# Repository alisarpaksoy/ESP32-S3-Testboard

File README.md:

# ESP32-S3 Testboard

## Overview

This project is a custom ESP32-S3 testboard designed in KiCad. The board was created as a compact development and testing platform for the ESP32-S3-WROOM module.

The board includes USB-C power and data connection, 3.3 V voltage regulation, boot and reset buttons, a user button, RGB LED, Qwiic I2C connector, GPIO headers, and an onboard Si7021-A20 temperature and humidity sensor.

The purpose of this project is to practice PCB design, ESP32-S3 hardware design, sensor integration, and GitHub-based engineering documentation.

## Main Features

* ESP32-S3-WROOM module
* USB-C connector for power and USB communication
* 5 V input from USB-C
* 3.3 V regulated power supply
* Boot and reset buttons
* User button
* RGB LED
* Si7021-A20 temperature and humidity sensor
* Qwiic I2C connector
* GPIO/SPI breakout headers
* ESD protection components
* Mounting holes
* ESP32-S3 antenna keepout area

## Hardware Description

### ESP32-S3 Module

The main microcontroller of the board is the ESP32-S3-WROOM module. It provides Wi-Fi, Bluetooth Low Energy, GPIO, USB, I2C, SPI, UART, PWM, ADC, and other peripheral interfaces.

The board exposes several ESP32-S3 pins through headers so the module can be used for testing and prototyping.

### Power Supply

The board is powered through the USB-C connector. The USB 5 V input is protected using a polyfuse and then regulated to 3.3 V using an LDO regulator.

The 3.3 V rail powers the ESP32-S3 module, Si7021 sensor, RGB LED, Qwiic connector, and supporting circuits.

### USB-C Interface

The USB-C connector provides power and USB data communication. The USB D+ and D− lines are connected to the ESP32-S3 USB pins for programming and serial communication.

### Boot and Reset Circuit

The board includes dedicated boot and reset buttons. The boot button is connected to GPIO0, and the reset button is connected to the ESP32-S3 enable/reset line.

These buttons allow the ESP32-S3 to be reset and placed into programming mode during firmware upload.

### Si7021 Temperature and Humidity Sensor

The board includes the Si7021-A20 digital temperature and humidity sensor. It communicates with the ESP32-S3 using the I2C bus.

This sensor can be used for:

* Temperature measurement
* Humidity measurement
* Environmental monitoring
* I2C communication testing

### Qwiic I2C Connector

A Qwiic connector is included for connecting external I2C modules. The connector provides:

* GND
* 3.3 V
* SDA
* SCL

Pull-up resistors are included on the I2C lines.

### RGB LED

The RGB LED is connected to ESP32-S3 GPIO pins through current-limiting resistors. It can be used for status indication, firmware testing, and GPIO output testing.

## Repository Structure

```text
ESP32-S3-Testboard/
│
├── README.md
├── .gitignore
│
├── kicad/
│   ├── ESP32-S3.kicad_pro
│   ├── ESP32-S3.kicad_sch
│   └── ESP32-S3.kicad_pcb
│
├── Images/
│   ├── schematic.png
│   ├── pcb_layout.png
│   └── pcb_3d_view.png
│
├── Documentation/
│   └── Datasheets/
│       ├── esp32-s3-wroom-1_wroom-1u_datasheet_en.pdf
│       └── Si7021-A20_datasheet.pdf
│
└── Manufacturing/
    ├── Gerbers/
    └── Drill/
```

## KiCad Project

The KiCad design files are located in the `kicad/` folder.

To open the project:

1. Install KiCad.
2. Open the `.kicad_pro` file.
3. Review the schematic and PCB layout.
4. Run ERC and DRC before modifying or manufacturing the board.

## Images

Project images are located in the `Images/` folder.

Included images:

* Schematic screenshot
* PCB layout screenshot
* 3D PCB render

## Manufacturing

Manufacturing files will be placed in the `Manufacturing/` folder.

Before ordering the PCB, the following checks should be completed:

* Electrical Rules Check
* Design Rules Check
* Gerber preview inspection
* Drill file verification
* USB-C footprint check
* ESP32-S3 footprint orientation check
* ESP32-S3 antenna keepout check
* Power trace width check
* I2C pull-up resistor verification

## Project Status

* [x] Schematic completed
* [x] PCB layout completed
* [x] ESP32-S3 module added
* [x] USB-C interface added
* [x] 3.3 V regulator added
* [x] Si7021 sensor added
* [x] Qwiic connector added
* [x] RGB LED added
* [ ] PCB manufactured
* [ ] Board assembled
* [ ] Power supply tested
* [ ] USB programming tested
* [ ] Si7021 sensor tested
* [ ] Example firmware added

## Author

Ali Sarp Aksoy
Mechatronics Engineering Student
Kraków, Poland

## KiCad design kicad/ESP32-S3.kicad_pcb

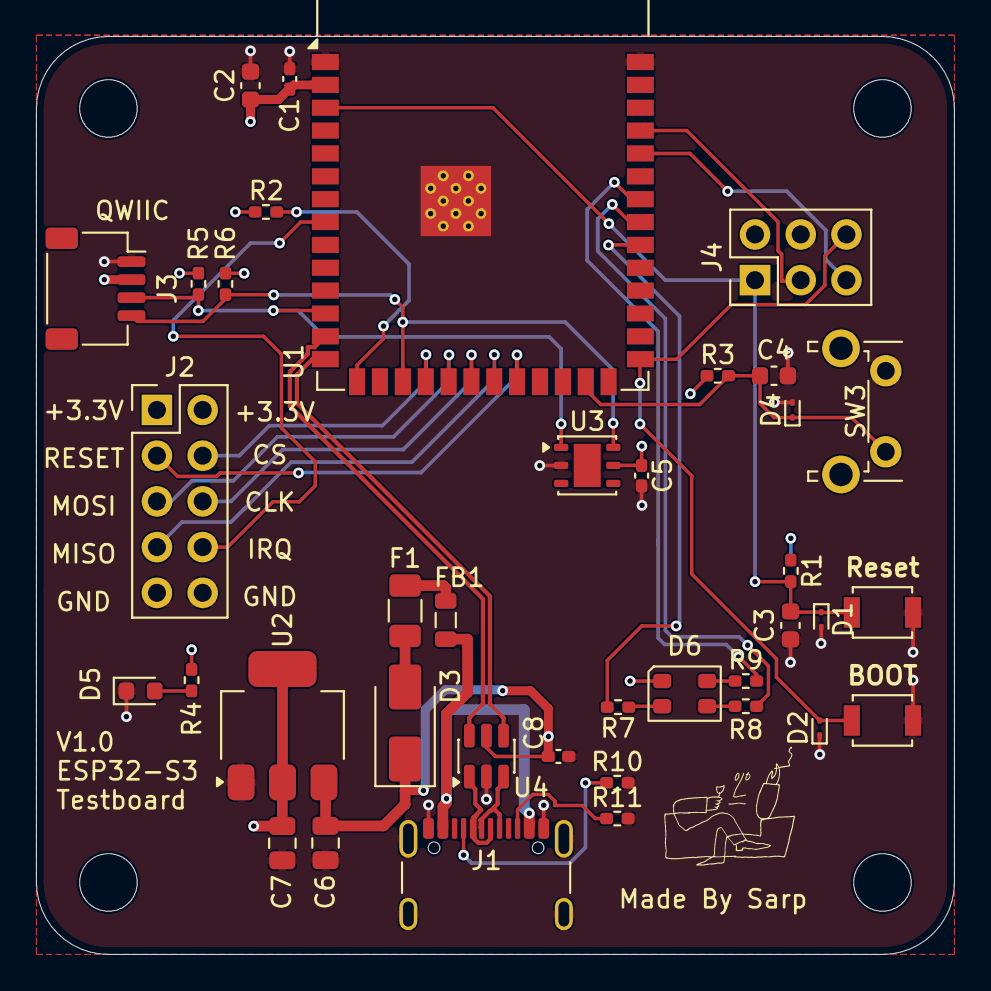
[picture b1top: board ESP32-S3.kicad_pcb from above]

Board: 4 copper layers, 51.0 x 51.0 mm, 42 parts (0 on the bottom side), 33 nets.

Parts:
C1, C5, C8: 100n; C_0402_1005Metric_Pad0.74x0.62mm_HandSolder
C2: 10u; C_0603_1608Metric
C3, C4: 1u; C_0603_1608Metric
C6, C7: 22u; C_0805_2012Metric
D1, D2, D4: ESD3.3; D_SOD-923
D3: 1N5817; D_SMA
D5: Green; LED_0603_1608Metric
D6: CLV1L-FKB; LED_Cree-PLCC4_3.2x2.8mm_CCW
F1: Polyfuse 1A; Fuse_1206_3216Metric
FB1: BLM21PG220; L_0805_2012Metric
H1, H2, H3, H4: MountingHole; MountingHole_3.2mm_M3
J1: USB_C_Receptacle_USB2.0_16P; USB_C_Receptacle_GCT_USB4105-xx-A_16P_TopMnt_Horizontal
J2: Conn_02x03_Odd_Even; PinHeader_2x05_P2.54mm_Vertical
J3: Conn_01x04; JST_SH_SM04B-SRSS-TB_1x04-1MP_P1.00mm_Horizontal
J4: Pin_2x5; PinHeader_2x03_P2.54mm_Vertical
R1, R2, R3: 10K; R_0402_1005Metric_Pad0.72x0.64mm_HandSolder
R4, R7, R8, R9: 1K; R_0402_1005Metric_Pad0.72x0.64mm_HandSolder
R5, R6: 2K2; R_0402_1005Metric_Pad0.72x0.64mm_HandSolder
R10, R11: 5.1K; R_0402_1005Metric_Pad0.72x0.64mm_HandSolder
SW1: BOOT; SW_SPST_B3U-1000P
SW2: Reset; SW_SPST_B3U-1000P
SW3: USER_SW; SW_Tactile_SPST_Angled_PTS645Vx31-2LFS
U1: ESP32-S3-WROOM-1
U2: LM1117DT-3.3; SOT-223
U3: Si7021-A20; DFN-6-1EP_3x3mm_P1mm_EP1.5x2.4mm
U4: USBLC6-2SC6; SOT-23-6

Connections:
+3.3V: C1.1, C2.1, C5.1, C7.1, D6.1 (A), J2.1, J2.2, J3.2, J4.2, R1.1, R2.2, R3.1, R4.1, R5.1, R6.1, U1.2 (3V3), U2.2 (VO), U2.4, U3.5 (VDD)
+5V: C6.1, C8.1, D3.1 (K), U2.3 (VI), U4.5 (VBUS)
/B_LED: R9.2, U1.34 (IO41)
/CC1: J1.A5 (CC1), R10.1
/CC2: J1.B5 (CC2), R11.1
/CLK: J2.6, U1.20 (IO12)
/CS: J2.4, U1.18 (IO10)
/D+: J1.A6 (D+), J1.B6 (D+), U4.3 (I/O2)
/D-: J1.A7 (D-), J1.B7 (D-), U4.1 (I/O1)
/ESP_EN: C3.1, D1.1 (A1), J4.1, R1.2, SW2.2 (B), U1.3 (EN)
/ESP_IO0: D2.2 (A2), J4.6, SW1.2 (B), U1.27 (IO0)
/ESP_RXD: J4.5, U1.36 (RXD0)
/ESP_TXD: J4.3, U1.37 (TXD0)
/G_LED: R8.2, U1.33 (IO40)
/IRQ: J2.8, U1.8 (IO15)
/MISO: J2.7, U1.21 (IO13)
/MOSI: J2.5, U1.19 (IO11)
/RESET: J2.3, U1.22 (IO14)
/R_LED: R7.2, U1.32 (IO39)
/SCL: J3.4, R6.2, U1.17 (IO9), U3.6 (SCL)
/SDA: J3.3, R5.2, U1.12 (IO8), U3.1 (SDA)
/USB_D+: U1.14 (USB_D+), U4.4 (I/O2)
/USB_D-: U1.13 (USB_D-), U4.6 (I/O1)
/USER_SW: C4.1, D4.1 (A1), R3.2, SW3.2 (B), U1.25 (IO48)
GND: C1.2, C2.2, C3.2, C4.2, C5.2, C6.2, C7.2, C8.2, D1.2 (A2), D2.1 (A1), D4.2 (A2), D5.1 (K), J1.A1 (GND), J1.A12 (GND), J1.B1 (GND), J1.B12 (GND), J1.SH (SHIELD), J2.9, J2.10, J3.1, J4.4, R10.2, R11.2, SW1.1 (A), SW2.1 (A), SW3.1 (A), U1.1 (GND), U1.40 (GND), U1.41 (GND), U2.1 (GND), U3.2 (GND), U4.2 (GND)
unnamed: D3.2 (A), F1.1
unnamed: D5.2 (A), R4.2
unnamed: D6.4 (BK), R9.1
unnamed: D6.3 (GK), R8.1
unnamed: D6.2 (RK), R7.1
unnamed: FB1.1, J1.A4 (VBUS), J1.A9 (VBUS), J1.B4 (VBUS), J1.B9 (VBUS)
unnamed: F1.2, FB1.2
unnamed: R2.1, U1.15 (IO3)

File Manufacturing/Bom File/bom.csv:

Designator,Footprint,Quantity,Value,LCSC Part #
"C1, C5, C8",0402,3,100n,
C2,0603,1,10u,
"C3, C4",0603,2,1u,
"C6, C7",0805,2,22u,
"D1, D2, D4",D_SOD-923,3,ESD3.3,
D3,D_SMA,1,1N5817,
D5,0603,1,Green,
D6,LED_Cree-PLCC4_3.2x2.8mm_CCW,1,CLV1L-FKB,
F1,1206,1,Polyfuse 1A,
FB1,0805,1,BLM21PG220,
J1,USB_C_Receptacle_GCT_USB4105-xx-A_16P_TopMnt_Horizontal,1,USB_C_Receptacle_USB2.0_16P,
J2,PinHeader_2x05_P2.54mm_Vertical,1,Conn_02x03_Odd_Even,
J3,JST_SH_SM04B-SRSS-TB_1x04-1MP_P1.00mm_Horizontal,1,Conn_01x04,
J4,PinHeader_2x03_P2.54mm_Vertical,1,Pin_2x5,
"R1, R2, R3",0402,3,10K,
"R10, R11",0402,2,5.1K,
"R4, R7, R8, R9",0402,4,1K,
"R5, R6",0402,2,2K2,
SW1,SW_SPST_B3U-1000P,1,BOOT,
SW2,SW_SPST_B3U-1000P,1,Reset,
SW3,SW_Tactile_SPST_Angled_PTS645Vx31-2LFS,1,USER_SW,
U1,ESP32-S3-WROOM-1,1,ESP32-S3-WROOM-1,
U2,SOT-223,1,LM1117DT-3.3,
U3,DFN-6-1EP_3x3mm_P1mm_EP1.5x2.4mm,1,Si7021-A20,
U4,SOT-23-6,1,USBLC6-2SC6,

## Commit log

2026-06-28 Kicad with required files
2026-06-28 Create Images
2026-06-28 Create Screenshots
